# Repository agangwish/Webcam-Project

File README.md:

# Webcam Project - Belobog Studios

This repository contains the code and PCB files for the Pan-Tilt-Zoom camera developed with Caleb Burton during the course of EECS 495 (Engineering System Design) at Northwestern University

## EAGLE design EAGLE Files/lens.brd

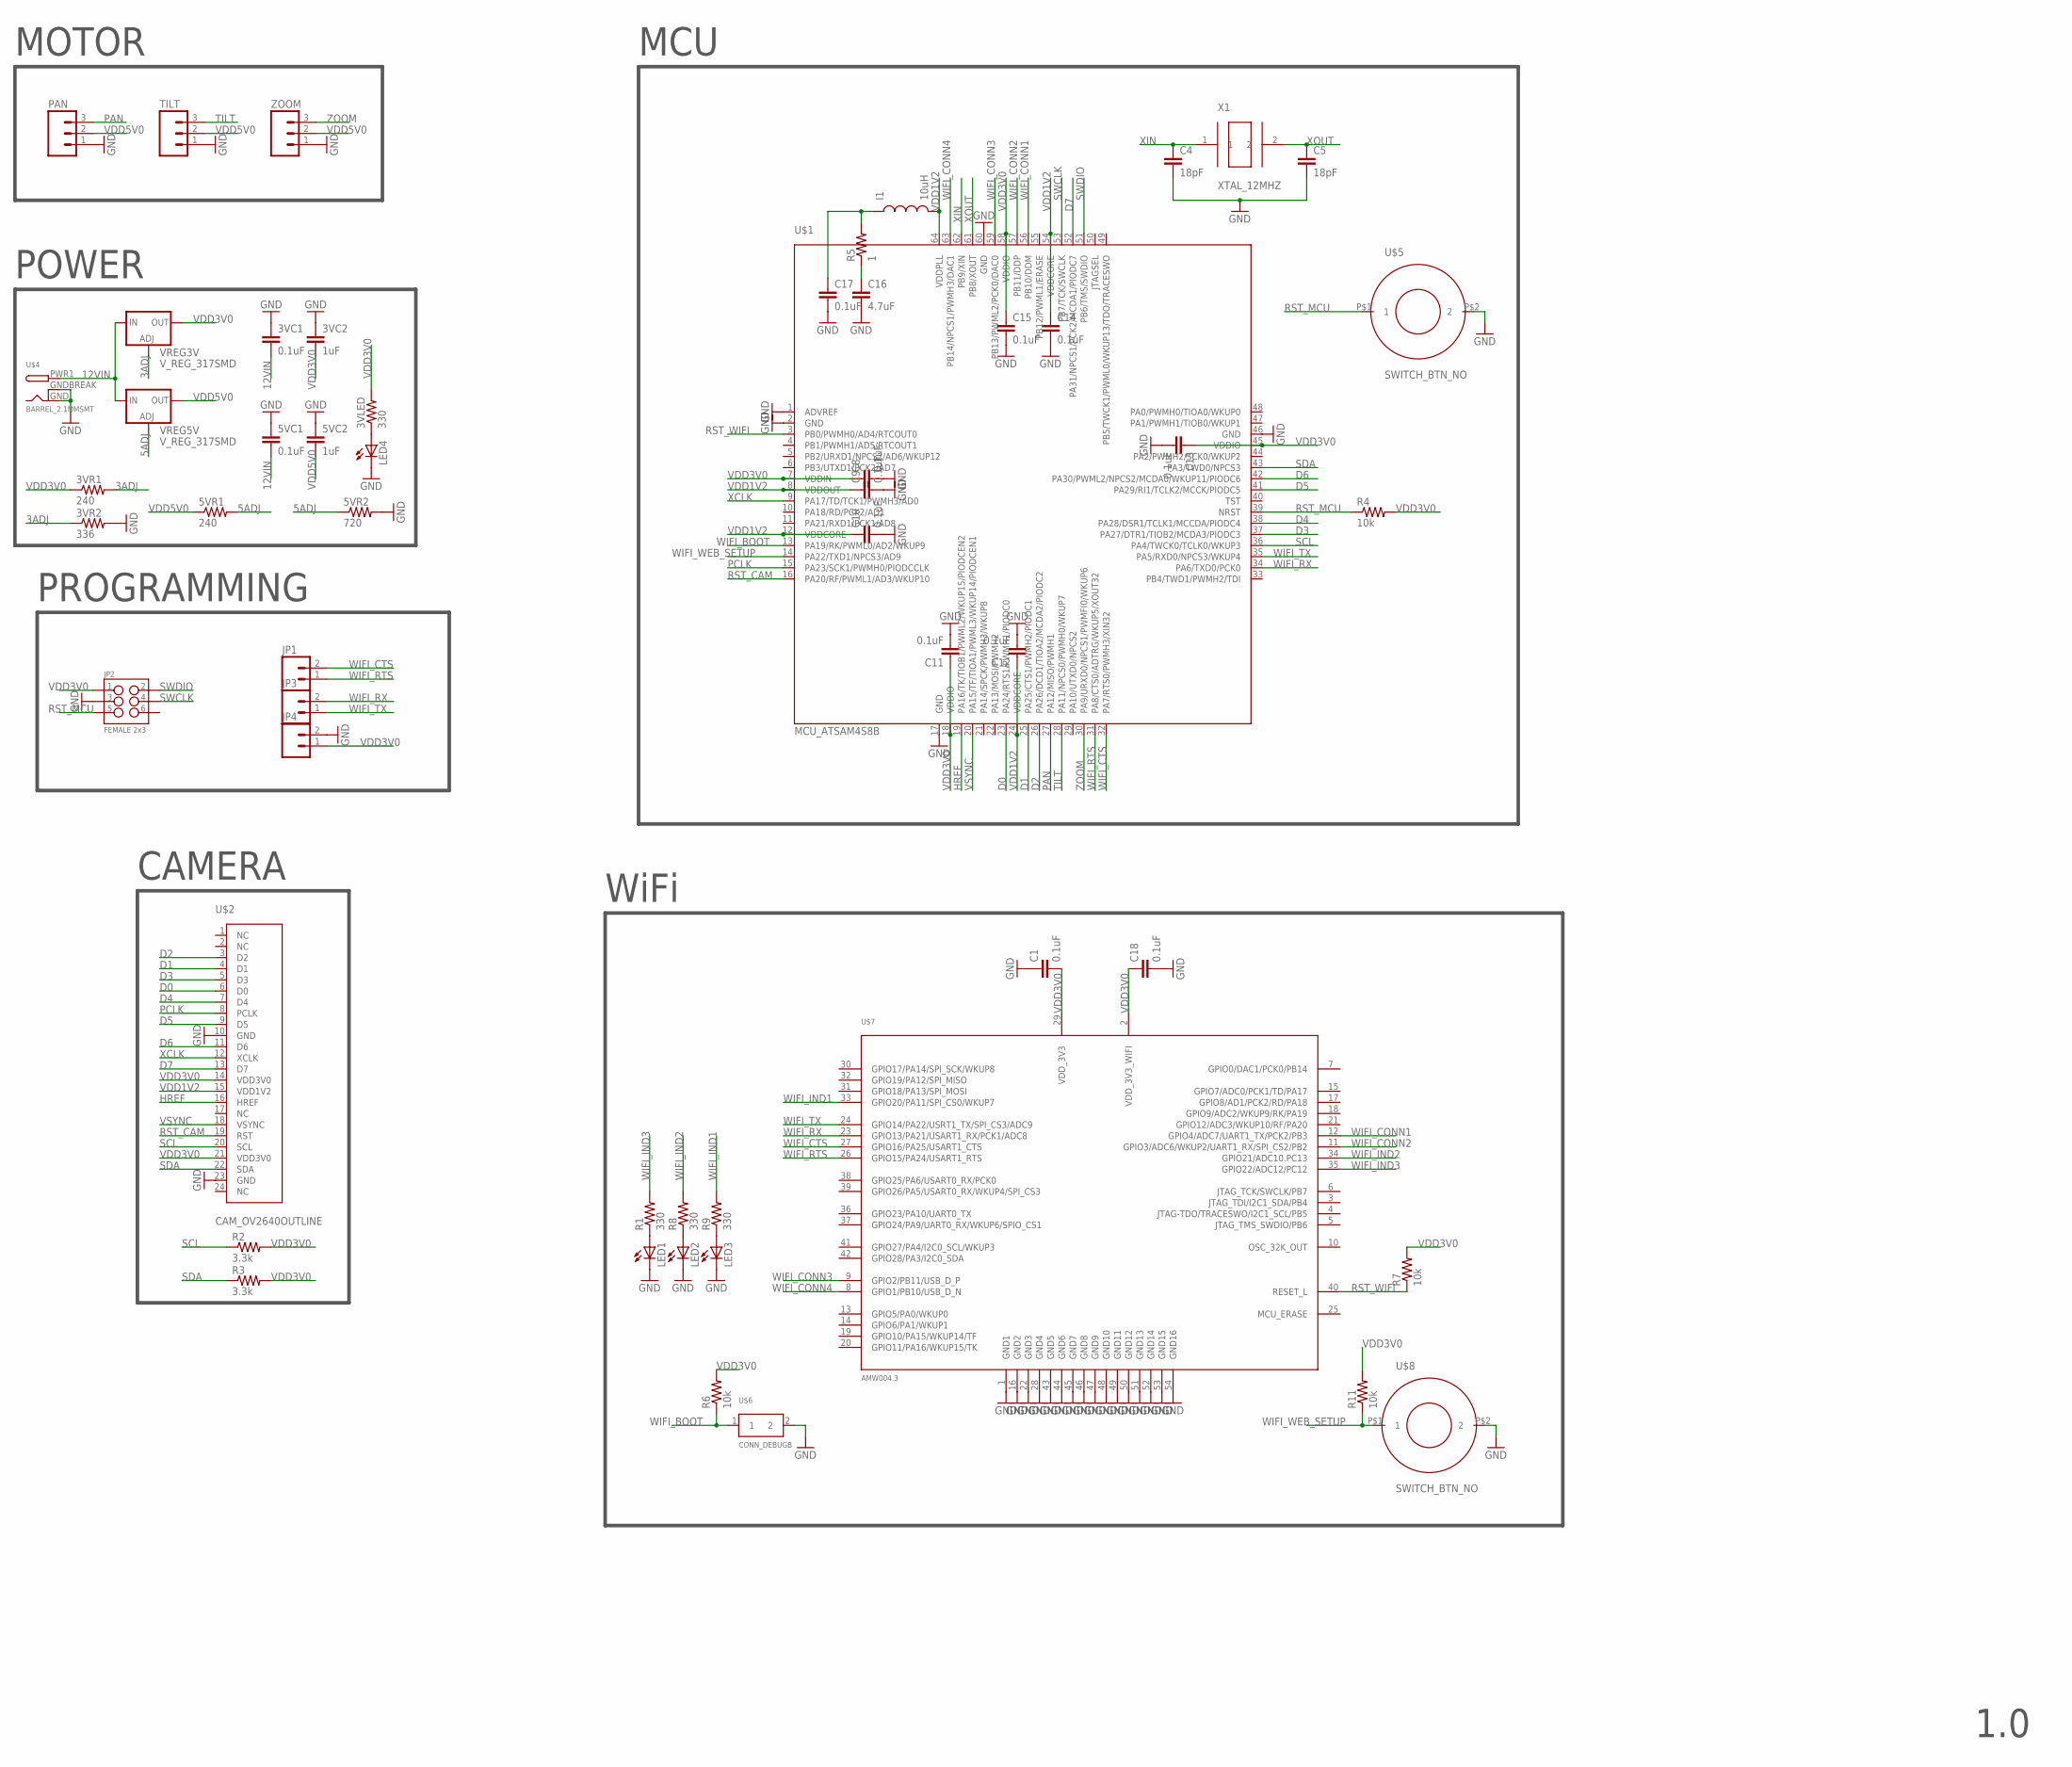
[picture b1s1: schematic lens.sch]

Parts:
3VC1, 5VC1: 0.1uF; 0805
3VC2, 5VC2: 1uF; 0805
3VLED: 330; 0805
3VR1, 5VR1: 240; 0805
3VR2: 336; 0805
5VR2: 720; 0805
C1, C8, C9, C10, C11, C12, C13, C14, C15, C17, C18: 0.1uF; 0805
C4, C5: 18pF; 0805
C16: 4.7uF; 0805
I1: 10uH; 0805
JP1, JP3, JP4: M02PTH; 1X02
JP2: FEMALE 2x3; 2X3
LED1, LED2, LED3, LED4: LED0603; LED-0603
PAN: M03PTH; 1X03
R1, R8, R9: 330; 0805
R2, R3: 3.3k; 0805
R4, R6, R7, R11: 10k; 0805
R5: 1; 0805
TILT: M03PTH; 1X03
U$1: MCU_ATSAM4S8B; QFP50P1200X1200X160-64N
U$2: CAM_OV2640OUTLINE; CAM_CONN
U$4: BARREL_2.1MMSMT; DCJACK_2MM_SMT
U$5, U$8: SWITCH_BTN_NO; BTN_2
U$6: CONN_DEBUGB; 1X2_SMALL_SMD
U$7: AMW004.3; AMW004
VREG3V, VREG5V: V_REG_317SMD; SOT223
X1: XTAL_12MHZ; ABM7-16.000MHZ-D2Y-T
ZOOM: M03PTH; 1X03

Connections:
3ADJ: 3VR1.2, 3VR2.1, VREG3V.1 (ADJ)
5ADJ: 5VR1.2, 5VR2.1, VREG5V.1 (ADJ)
12VIN: 3VC1.2, 5VC1.2, U$4.PWR1 (PWR), VREG3V.3 (IN), VREG5V.3 (IN)
D0: U$1.23 (PA24/RTS1/PWMH1/PIODC0), U$2.6 (D0)
D1: U$1.25 (PA25/CTS1/PWMH2/PIODC1), U$2.4 (D1)
D2: U$1.26 (PA26/DCD1/TIOA2/MCDA2/PIODC2), U$2.3 (D2)
D3: U$1.37 (PA27/DTR1/TIOB2/MCDA3/PIODC3), U$2.5 (D3)
D4: U$1.38 (PA28/DSR1/TCLK1/MCCDA/PIODC4), U$2.7 (D4)
D5: U$1.41 (PA29/RI1/TCLK2/MCCK/PIODC5), U$2.9 (D5)
D6: U$1.42 (PA30/PWML2/NPCS2/MCDA0/WKUP11/PIODC6), U$2.11 (D6)
D7: U$1.52 (PA31/NPCS1/PCK2/MCDA1/PIODC7), U$2.13 (D7)
GND: 3VC1.1, 3VC2.1, 3VR2.2, 5VC1.1, 5VC2.1, 5VR2.2, C1.1, C4.2, C5.2, C8.2, C9.2, C10.2, C11.2, C12.2, C13.2, C14.2, C15.2, C16.2, C17.2, C18.2, JP2.3, JP4.2, LED1.C, LED2.C, LED3.C, LED4.C, PAN.1, TILT.1, U$1.1 (ADVREF), U$1.2 (GND), U$1.17 (GND), U$1.46 (GND), U$1.60 (GND), U$2.10 (GND), U$2.23 (GND), U$4.GND, U$4.GNDBREAK, U$5.P$2 (2), U$6.2, U$7.1 (GND1), U$7.16 (GND2), U$7.22 (GND3), U$7.28 (GND4), U$7.43 (GND5), U$7.44 (GND6), U$7.45 (GND7), U$7.46 (GND8), U$7.47 (GND9), U$7.48 (GND10), U$7.49 (GND11), U$7.50 (GND12), U$7.51 (GND13), U$7.52 (GND14), U$7.53 (GND15), U$7.54 (GND16), U$8.P$2 (2), ZOOM.1
HREF: U$1.19 (PA16/TK/TIOB1/PWML2/WKUP15/PIODCEN2), U$2.16 (HREF)
unnamed: C17.1, I1.1, R5.2
unnamed: C16.1, R5.1
unnamed: LED1.A, R1.1
unnamed: LED2.A, R8.1
unnamed: LED3.A, R9.1
unnamed: 3VLED.1, LED4.A
PAN: PAN.3, U$1.27 (PA12/MISO/PWMH1)
PCLK: U$1.15 (PA23/SCK1/PWMH0/PIODCCLK), U$2.8 (PCLK)
RST_CAM: U$1.16 (PA20/RF/PWML1/AD3/WKUP10), U$2.19 (RST)
RST_MCU: JP2.5, R4.1, U$1.39 (NRST), U$5.P$1 (1)
RST_WIFI: R7.1, U$1.3 (PB0/PWMH0/AD4/RTCOUT0), U$7.40 (RESET_L)
SCL: R2.1, U$1.36 (PA4/TWCK0/TCLK0/WKUP3), U$2.20 (SCL)
SDA: R3.1, U$1.43 (PA3/TWD0/NPCS3), U$2.22 (SDA)
SWCLK: JP2.4, U$1.53 (PB7/TCK/SWCLK)
SWDIO: JP2.2, U$1.51 (PB6/TMS/SWDIO)
TILT: TILT.3, U$1.28 (PA11/NPCS0/PWMH0/WKUP7)
VDD1V2: C9.1, C10.1, C12.1, C14.1, I1.2, U$1.8 (VDDOUT), U$1.12 (VDDCORE), U$1.24 (VDDCORE), U$1.54 (VDDCORE), U$1.64 (VDDPLL), U$2.15 (VDD1V2)
VDD3V0: 3VC2.2, 3VLED.2, 3VR1.1, C1.2, C8.1, C11.1, C13.1, C15.1, C18.1, JP2.1, JP4.1, R2.2, R3.2, R4.2, R6.2, R7.2, R11.2, U$1.7 (VDDIN), U$1.18 (VDDIO), U$1.45 (VDDIO), U$1.58 (VDDIO), U$2.14 (VDD3V0), U$2.21 (VDD3V0), U$7.2 (VDD_3V3_WIFI), U$7.29 (VDD_3V3), VREG3V.2 (OUT)
VDD5V0: 5VC2.2, 5VR1.1, PAN.2, TILT.2, VREG5V.2 (OUT), ZOOM.2
VSYNC: U$1.20 (PA15/TF/TIOA1/PWML3/WKUP14/PIODCEN1), U$2.18 (VSYNC)
WIFI_BOOT: R6.1, U$1.13 (PA19/RK/PWML0/AD2/WKUP9), U$6.1
WIFI_CONN1: U$1.56 (PB10/DDM), U$7.12 (GPIO4/ADC7/UART1_TX/PCK2/PB3)
WIFI_CONN2: U$1.57 (PB11/DDP), U$7.11 (GPIO3/ADC6/WKUP2/UART1_RX/SPI_CS2/PB2)
WIFI_CONN3: U$1.59 (PB13/PWML2/PCK0/DAC0), U$7.9 (GPIO2/PB11/USB_D_P)
WIFI_CONN4: U$1.63 (PB14/NPCS1/PWMH3/DAC1), U$7.8 (GPIO1/PB10/USB_D_N)
WIFI_CTS: JP1.2, U$1.32 (PA7/RTS0/PWMH3/XIN32), U$7.27 (GPIO16/PA25/USART1_CTS)
WIFI_IND1: R9.2, U$7.33 (GPIO20/PA11/SPI_CS0/WKUP7)
WIFI_IND2: R8.2, U$7.34 (GPIO21/ADC10.PC13)
WIFI_IND3: R1.2, U$7.35 (GPIO22/ADC12/PC12)
WIFI_RTS: JP1.1, U$1.31 (PA8/CTS0/ADTRG/WKUP5/XOUT32), U$7.26 (GPIO15/PA24/USART1_RTS)
WIFI_RX: JP3.2, U$1.34 (PA6/TXD0/PCK0), U$7.23 (GPIO13/PA21/USART1_RX/PCK1/ADC8)
WIFI_TX: JP3.1, U$1.35 (PA5/RXD0/NPCS3/WKUP4), U$7.24 (GPIO14/PA22/USRT1_TX/SPI_CS3/ADC9)
WIFI_WEB_SETUP: R11.1, U$1.14 (PA22/TXD1/NPCS3/AD9), U$8.P$1 (1)
XCLK: U$1.9 (PA17/TD/TCK1/PWMH3/AD0), U$2.12 (XCLK)
XIN: C4.1, U$1.62 (PB9/XIN), X1.1
XOUT: C5.1, U$1.61 (PB8/XOUT), X1.2
ZOOM: U$1.30 (PA9/URXD0/NPCS1/PWMFI0/WKUP6), ZOOM.3

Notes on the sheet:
POWER
PROGRAMMING
CAMERA
WiFi
MCU
1.0
MOTOR

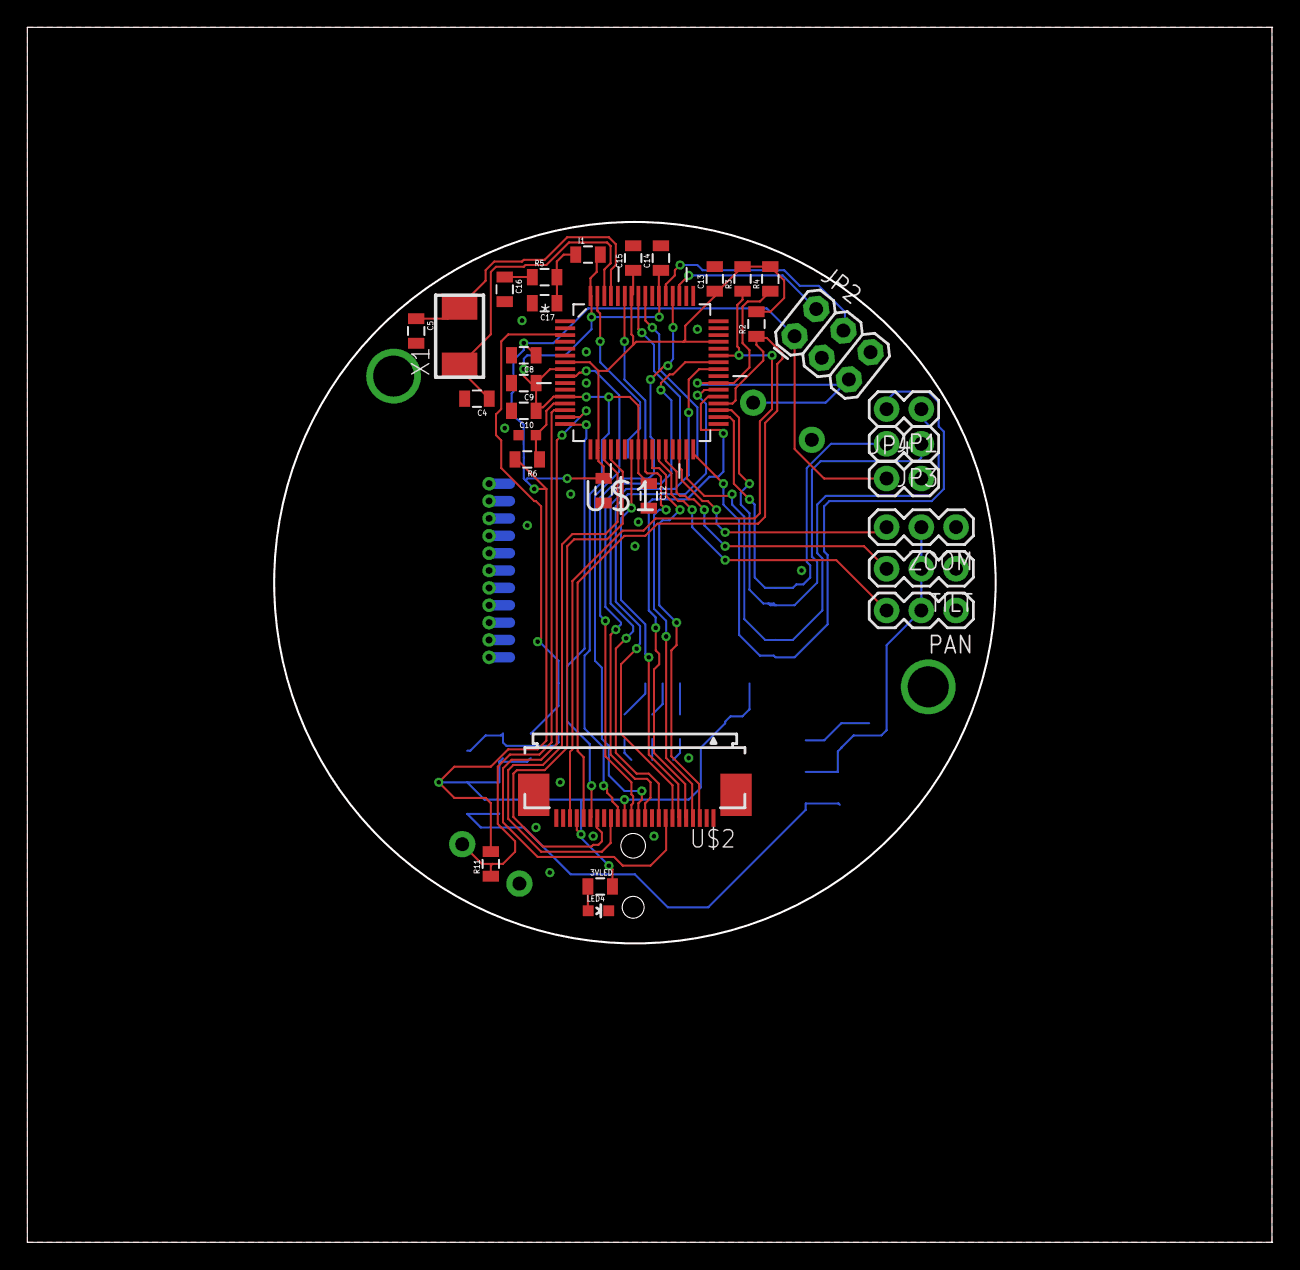
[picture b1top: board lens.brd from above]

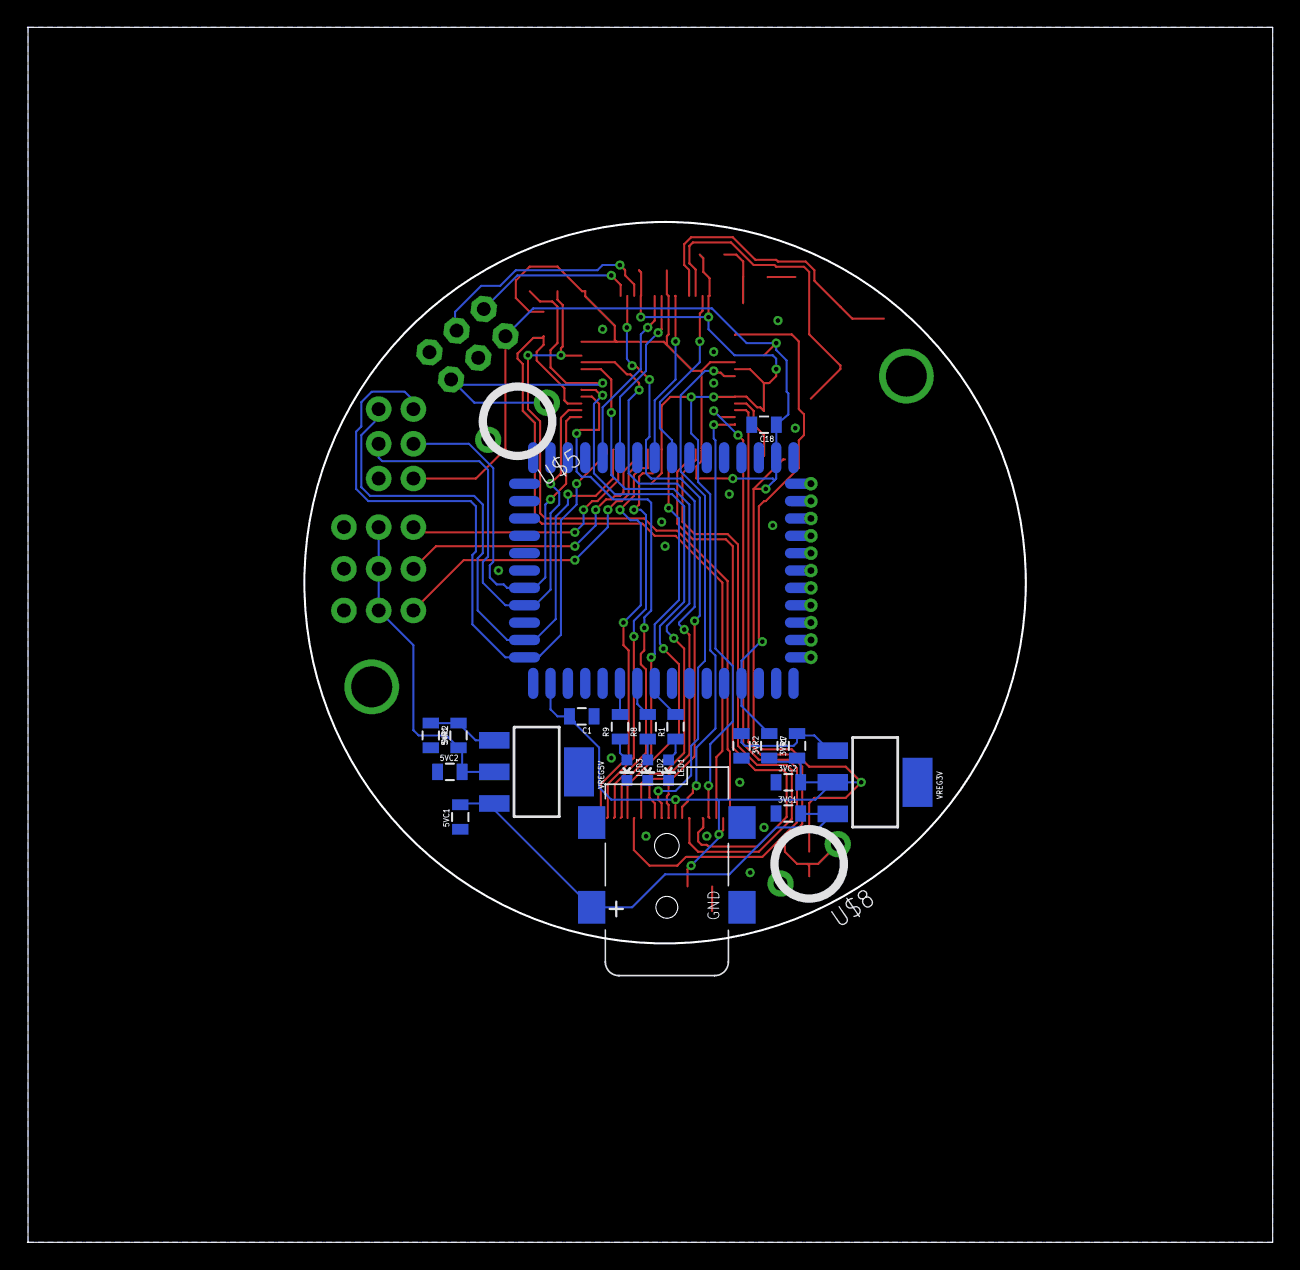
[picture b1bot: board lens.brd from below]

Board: 2 copper layers, 91.0 x 88.7 mm, 55 parts (23 on the bottom side), 50 nets.

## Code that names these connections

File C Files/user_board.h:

/**
 * \file
 *
 * \brief User board definition template
 *
 */

 /* This file is intended to contain definitions and configuration details for
 * features and devices that are available on the board, e.g., frequency and
 * startup time for an external crystal, external memory devices, LED and USART
 * pins.
 */


#ifndef USER_BOARD_H
#define USER_BOARD_H

#include <conf_board.h>

#include "compiler.h"
#include "system_sam4s.h"


/*----------------------------------------------------------------------------*/

#define BOARD_NUM_OF_LED 3

/** PWM LED0 pin definitions. */
//#define PIN_PWM_LED0_GPIO    PIO_PB13_IDX // periph A
#define PIN_PWM_LED0_GPIO    PIO_PA12_IDX // PAN
#define PIN_PWM_LED0_FLAGS   (PIO_PERIPH_B | PIO_DEFAULT)
#define PIN_PWM_LED0_CHANNEL PWM_CHANNEL_0

/** PWM LED1 pin definitions.*/
//#define PIN_PWM_LED1_GPIO    PIO_PA20_IDX // periph B
#define PIN_PWM_LED1_GPIO    PIO_PA11_IDX // TILT
#define PIN_PWM_LED1_FLAGS   (PIO_PERIPH_B | PIO_DEFAULT)
#define PIN_PWM_LED1_CHANNEL PWM_CHANNEL_1

/** PWM LED2 pin definitions. */
//#define PIN_PWM_LED2_GPIO    PIO_PA19_IDX // periph B
#define PIN_PWM_LED2_GPIO    PIO_PB4_IDX // ZOOM // Doesn't work since PA9 is a PWMFL line, which is input only
#define PIN_PWM_LED2_FLAGS   (PIO_PERIPH_B | PIO_DEFAULT)
#define PIN_PWM_LED2_CHANNEL PWM_CHANNEL_2

#endif // USER_BOARD_H

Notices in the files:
parts and their libraries:
SparkFun: Licensing: CC v3.0 Share-Alike You are welcome to use this library for commercial purposes.
SparkFun-Connectors: Licensing: Creative Commons ShareAlike 4.0 International - https://creativecommons.org/licenses/by-sa/4.0
